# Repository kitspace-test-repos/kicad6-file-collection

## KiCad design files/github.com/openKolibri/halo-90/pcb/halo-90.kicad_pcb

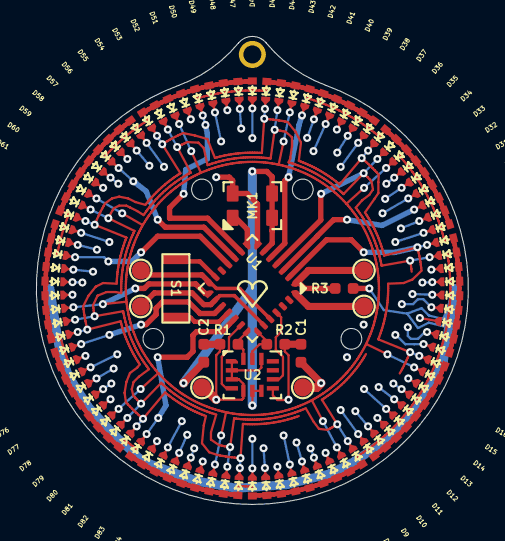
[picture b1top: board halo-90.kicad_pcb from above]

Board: 4 copper layers, 24.0 x 26.0 mm, 111 parts (1 on the bottom side), 23 nets.

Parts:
BT1: CR-2032; BAT-HLD-001-HALO
C1: 0u1; C-0402
C2: 1u; C-0402
D1, D2, D3, D4, D5, D6, D7, D8, D9, D10, D11, D12, D13, D14, D15, D16, D17, D18, D19, D20, D21, D22, D23, D24, D25, D26, D27, D28, D29, D30, D31, D32, D33, D34, D35, D36, D37, D38, D39, D40, D41, D42, D43, D44, D45, D46, D47, D48, D49, D50, D51, D52, D53, D54, D55, D56, D57, D58, D59, D60, D61, D62, D63, D64, D65, D66, D67, D68, D69, D70, D71, D72, D73, D74, D75, D76, D77, D78, D79, D80, D81, D82, D83, D84, D85, D86, D87, D88, D89, D90: LED; D-0402
H1: frenchEarwire; earringHookWire
MH1, MH2, MH3, MH4: toolingHole; 1.152mm-ToolingHole
MK1: SPW2430HR5H-B
R1, R2, R3: 10k; R-0402
S1: KXT3
TP1: TX; TestPoint_Pad_D1.0mm
TP2: SWIM; TestPoint_Pad_D1.0mm
TP3: GND; TestPoint_Pad_D1.0mm
TP4: 3V0; TestPoint_Pad_D1.0mm
TP5: RST; TestPoint_Pad_D1.0mm
TP6: RX; TestPoint_Pad_D1.0mm
U1: UFQFPN28
U2: LSM6DSM; LGA-14_3x2.5mm_6-6

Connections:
+3V: BT1.1 (+), C1.1, C2.1, MK1.4 (VDD), R1.2, R2.2, R3.1, TP4.1, U1.7 (VDD), U2.1 (SDO/SA0), U2.2 (SDX), U2.3 (SCX), U2.5 (VDDIO), U2.8 (VDD), U2.12 (CS)
CPX-0: D1.2 (K), D2.2 (K), D3.2 (K), D4.2 (K), D5.2 (K), D6.2 (K), D7.2 (K), D8.2 (K), D9.2 (K), D18.1 (A), D27.1 (A), D36.1 (A), D45.1 (A), D54.1 (A), D63.1 (A), D72.1 (A), D81.1 (A), D90.1 (A), U1.2 (PA2)
CPX-1: D9.1 (A), D10.2 (K), D11.2 (K), D12.2 (K), D13.2 (K), D14.2 (K), D15.2 (K), D16.2 (K), D17.2 (K), D18.2 (K), D26.1 (A), D35.1 (A), D44.1 (A), D53.1 (A), D62.1 (A), D71.1 (A), D80.1 (A), D89.1 (A), U1.4 (PA4)
CPX-2: D8.1 (A), D17.1 (A), D19.2 (K), D20.2 (K), D21.2 (K), D22.2 (K), D23.2 (K), D24.2 (K), D25.2 (K), D26.2 (K), D27.2 (K), D34.1 (A), D43.1 (A), D52.1 (A), D61.1 (A), D70.1 (A), D79.1 (A), D88.1 (A), U1.15 (PB3)
CPX-3: D7.1 (A), D16.1 (A), D25.1 (A), D28.2 (K), D29.2 (K), D30.2 (K), D31.2 (K), D32.2 (K), D33.2 (K), D34.2 (K), D35.2 (K), D36.2 (K), D42.1 (A), D51.1 (A), D60.1 (A), D69.1 (A), D78.1 (A), D87.1 (A), U1.5 (PA5)
CPX-4: D6.1 (A), D15.1 (A), D24.1 (A), D33.1 (A), D37.2 (K), D38.2 (K), D39.2 (K), D40.2 (K), D41.2 (K), D42.2 (K), D43.2 (K), D44.2 (K), D45.2 (K), D50.1 (A), D59.1 (A), D68.1 (A), D77.1 (A), D86.1 (A), U1.9 (PD1)
CPX-5: D5.1 (A), D14.1 (A), D23.1 (A), D32.1 (A), D41.1 (A), D46.2 (K), D47.2 (K), D48.2 (K), D49.2 (K), D50.2 (K), D51.2 (K), D52.2 (K), D53.2 (K), D54.2 (K), D58.1 (A), D67.1 (A), D76.1 (A), D85.1 (A), U1.10 (PD2)
CPX-6: D4.1 (A), D13.1 (A), D22.1 (A), D31.1 (A), D40.1 (A), D49.1 (A), D55.2 (K), D56.2 (K), D57.2 (K), D58.2 (K), D59.2 (K), D60.2 (K), D61.2 (K), D62.2 (K), D63.2 (K), D66.1 (A), D75.1 (A), D84.1 (A), U1.11 (PD3)
CPX-7: D3.1 (A), D12.1 (A), D21.1 (A), D30.1 (A), D39.1 (A), D48.1 (A), D57.1 (A), D64.2 (K), D65.2 (K), D66.2 (K), D67.2 (K), D68.2 (K), D69.2 (K), D70.2 (K), D71.2 (K), D72.2 (K), D74.1 (A), D83.1 (A), U1.3 (PA3)
CPX-8: D2.1 (A), D11.1 (A), D20.1 (A), D29.1 (A), D38.1 (A), D47.1 (A), D56.1 (A), D65.1 (A), D73.2 (K), D74.2 (K), D75.2 (K), D76.2 (K), D77.2 (K), D78.2 (K), D79.2 (K), D80.2 (K), D81.2 (K), D82.1 (A), U1.19 (PB7)
CPX-9: D1.1 (A), D10.1 (A), D19.1 (A), D28.1 (A), D37.1 (A), D46.1 (A), D55.1 (A), D64.1 (A), D73.1 (A), D82.2 (K), D83.2 (K), D84.2 (K), D85.2 (K), D86.2 (K), D87.2 (K), D88.2 (K), D89.2 (K), D90.2 (K), U1.17 (PB5)
GND: BT1.2 (-), C1.2, C2.2, MK1.2 (GND), MK1.3 (GND), TP3.1, U2.6 (GND), U2.7 (GND)
MIC: MK1.1 (Output), U1.8 (PD0)
unnamed: R3.2, TP5.1, U1.1 (~NRST)
unnamed: TP2.1, U1.28 (SWIM)
RX: TP6.1, U1.16 (PB4), U1.23 (PC2)
SCL: R2.1, U1.22 (PC1), U2.13 (SCL)
SDA: R1.1, U1.21 (PC0), U2.14 (SDA)
SW-A: S1.1, U1.13 (PB1)
SW-B: S1.2, U1.18 (PB6)
TX: TP1.1, U1.14 (PB2), U1.24 (PC3)
XL-INT1: U1.20 (PD4), U2.4 (INT1)
XL-INT2: U1.25 (PC4), U2.9 (INT2)

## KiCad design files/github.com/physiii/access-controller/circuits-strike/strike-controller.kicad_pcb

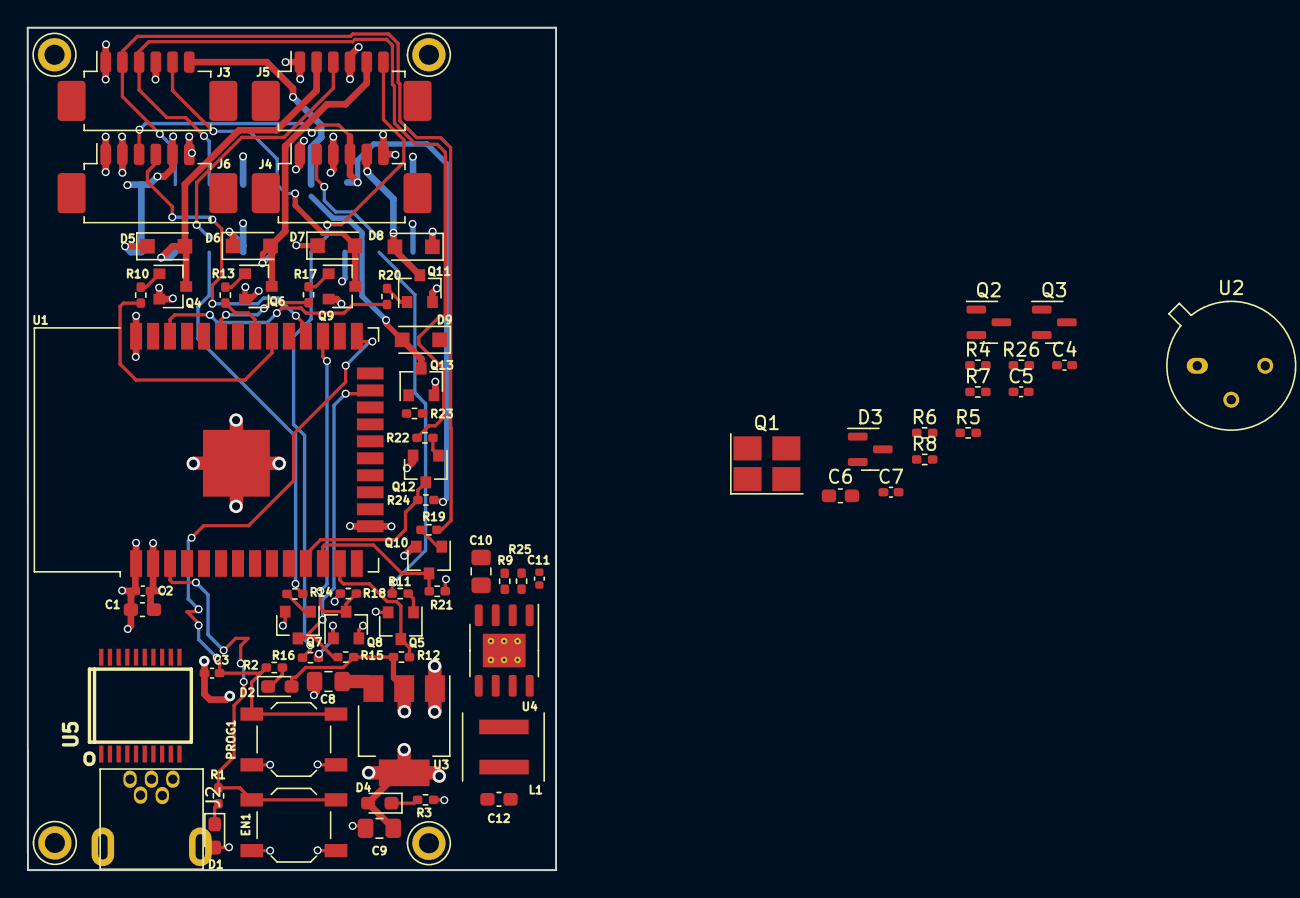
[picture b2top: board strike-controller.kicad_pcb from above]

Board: 4 copper layers, 39.5 x 63.0 mm, 78 parts (1 on the bottom side), 57 nets.

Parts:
C1: C_10uF; C_0603_1608Metric_Pad1.08x0.95mm_HandSolder
C2, C3: C_1uF; C_0402_1005Metric_Pad0.74x0.62mm_HandSolder
C4, C5: C_27pF_0402; C_0402_1005Metric_Pad0.74x0.62mm_HandSolder
C6, C12: C_22uF; C_0603_1608Metric_Pad1.08x0.95mm_HandSolder
C7: C_100nF_0402; C_0402_1005Metric_Pad0.74x0.62mm_HandSolder
C8, C9, C10: C_10uF; C_0805_2012Metric_Pad1.18x1.45mm_HandSolder
C11: 22nF; C_0402_1005Metric
D1, D2: LED_G; D_0603_1608Metric_Pad1.05x0.95mm_HandSolder
D3: BAT54C; SOT-23
D4: LED_G; LED_0603_1608Metric_Pad1.05x0.95mm_HandSolder
D5, D6, D7, D8, D9: D_SM4007PL; D_SOD-123F
EN1: SW_PUSH_SM; SW_SPST_TL3342
J1: Conn_02x09_Odd_Even; PinHeader_2x09_P2.54mm_Vertical_SMD
J2: USB_MINI_B; USB-mini-B-0548190519
J3, J4, J5, J6: Molex_Blade_6pin; Molex_PicoBlade_53261-0671_1x06-1MP_P1.25mm_Horizontal
J7, J8, J9, J10: Conn_01x01_Female; Mount_Hole_1p5
L1: 10uH; L_4x4
PROG1: SW_PUSH_SM; SW_SPST_TL3342
Q1: Crystal_12Mhz; Crystal_SMD_3225-4Pin_3.2x2.5mm_HandSoldering
Q2: Q_SS8050; SOT-23
Q3: Q_SS8550; SOT-23
Q4, Q5, Q6, Q7, Q8, Q9, Q10, Q11, Q12, Q13: Q_MMBT5551; SOT-23
R1, R2, R4, R5, R26: R_10K_0402; R_0402_1005Metric_Pad0.72x0.64mm_HandSolder
R3, R6, R7, R11, R12, R14, R15, R16, R18, R19, R21, R22, R24: R_1K_0402; R_0402_1005Metric_Pad0.72x0.64mm_HandSolder
R8: R_220_0402; R_0402_1005Metric_Pad0.72x0.64mm_HandSolder
R9: 49.9K; R_0402_1005Metric_Pad0.72x0.64mm_HandSolder
R10, R13, R17, R20, R23: R_100; R_0402_1005Metric_Pad0.72x0.64mm_HandSolder
R25: 19K; R_0402_1005Metric_Pad0.72x0.64mm_HandSolder
U1: ESP32-WROOM-32
U2: PIR-DIGITAL; TO-5-3
U3: REG_AMS1117-3.3; SOT-223-3_TabPin2
U4: REG_MT2492; SOIC-8-1EP_3.9x4.9mm_P1.27mm_EP2.514x3.2mm_ThermalVias
U5: CH340T(SSOP20W); SSOP-20W

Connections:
+3V3: C1.1, C2.1, C9.1, D1.2 (A), D2.2 (A), D4.2 (A), J1.13, J4.4, J6.3, R12.2, R15.2, R18.2, R21.2, R24.2, R26.2, U1.2 (VDD), U3.2 (Vout)
/5V: C6.1, C8.1, C12.1, J2.1 (VBUS), L1.2, R4.1, R9.1, U3.3 (Vin), U5.19 (VCC)
/AUX: D9.2 (A), J1.11, J3.6, Q13.3 (C)
/AUX_IO: R23.1, U1.37 (IO23)
/BUZZER1: D8.2 (A), J1.15, J4.5, Q11.3 (C)
/BUZZER1_IO: R20.1, U1.36 (IO22)
/CONTACT1: J1.6, J5.3, R14.2
/CONTACT1_IO: Q7.3 (C), R15.1, U1.23 (IO15)
/CONTACT2: J1.12, J5.6, R16.2
/CONTACT2_IO: Q8.3 (C), R18.1, U1.27 (IO16)
/ESP_EN: EN1.1, Q2.3 (C), R1.1, U1.3 (EN)
/EXIT: J1.16, J4.2, R11.2
/EXIT_IO: Q5.3 (C), R12.1, U1.13 (IO14)
/IO2: D3.2 (A2), U1.24 (IO2)
/IO17: J6.4, U1.28 (IO17)
/KEYPAD_PUSH: D7.2 (A), J1.9, J3.5, Q9.3 (C)
/KEYPAD_PUSH_IO: R17.1, U1.33 (IO21)
/LOCK1: D5.2 (A), J1.4, J5.2, Q4.3 (C)
/LOCK1_IO: R10.1, U1.30 (IO18)
/LOCK2: D6.2 (A), J1.10, J5.5, Q6.3 (C)
/LOCK2_IO: R13.1, U1.31 (IO19)
/POWER: C10.1, D5.1 (K), D6.1 (K), D7.1 (K), D8.1 (K), D9.1 (K), J1.1, J1.2, J1.8, J1.14, J3.1, J4.1, J5.1, J5.4, J6.2, J6.5, U4.4 (EN), U4.5 (VIN)
/PROG: C3.1, D3.1 (A1), PROG1.1, R2.1, U1.25 (IO0)
/RX: R5.2, R26.1, U1.34 (RXD0/IO3), U5.3 (TXD)
/TX: R4.2, U1.35 (TXD0/IO1), U5.4 (RXD)
/USB/D+: J2.3 (D+), U5.6 (UD+)
/USB/D-: J2.2 (D-), U5.7 (UD-)
/USB/D_Com: D3.3 (CC), R8.1
/WG_D0: J1.3, J3.2, R19.2
/WG_D0_IO: Q10.3 (C), R21.1, U1.12 (IO27)
/WG_D1: J1.5, J3.3, R22.2
/WG_D1_IO: Q12.3 (C), R24.1, U1.11 (IO26)
GND: C1.2, C2.2, C3.2, C4.2, C5.2, C6.2, C7.2, C8.2, C9.2, C10.2, C12.2, EN1.2, J1.7, J1.17, J1.18, J2.5 (GND), J3.4, J4.3, J4.6, J6.1, J6.6, J7.1, J8.1, J9.1, J10.1, PROG1.2, Q1.2 (case), Q1.4 (case), Q4.2 (E), Q5.2 (E), Q6.2 (E), Q7.2 (E), Q8.2 (E), Q9.2 (E), Q10.2 (E), Q11.2 (E), Q12.2 (E), Q13.2 (E), R3.2, R25.2, U1.1 (GND), U1.15 (GND), U1.38 (GND), U1.39 (GND), U3.1 (GND), U4.2 (GND), U5.8 (GND)
unnamed: C4.1, Q1.1, U5.9 (XI)
unnamed: C5.1, Q1.3, U5.10 (XO)
unnamed: C7.1, R5.1, U5.5 (V3)
unnamed: C11.1, U4.1 (BS)
unnamed: C11.2, L1.1, U4.6 (SW)
unnamed: D1.1 (K), R1.2
unnamed: D2.1 (K), R2.2
unnamed: D4.1 (K), R3.1
unnamed: Q2.1 (B), R6.1
unnamed: Q2.2 (E), R7.2, U5.16 (RTS#)
unnamed: Q3.1 (B), R7.1
unnamed: Q3.2 (E), R8.2
unnamed: Q3.3 (C), R6.2, U5.15 (DTR#)
unnamed: Q4.1 (B), R10.2
unnamed: Q5.1 (B), R11.1
unnamed: Q6.1 (B), R13.2
unnamed: Q7.1 (B), R14.1
unnamed: Q8.1 (B), R16.1
unnamed: Q9.1 (B), R17.2
unnamed: Q10.1 (B), R19.1
unnamed: Q11.1 (B), R20.2
unnamed: Q12.1 (B), R22.1
unnamed: Q13.1 (B), R23.2
unnamed: R9.2, R25.1, U4.3 (FB)

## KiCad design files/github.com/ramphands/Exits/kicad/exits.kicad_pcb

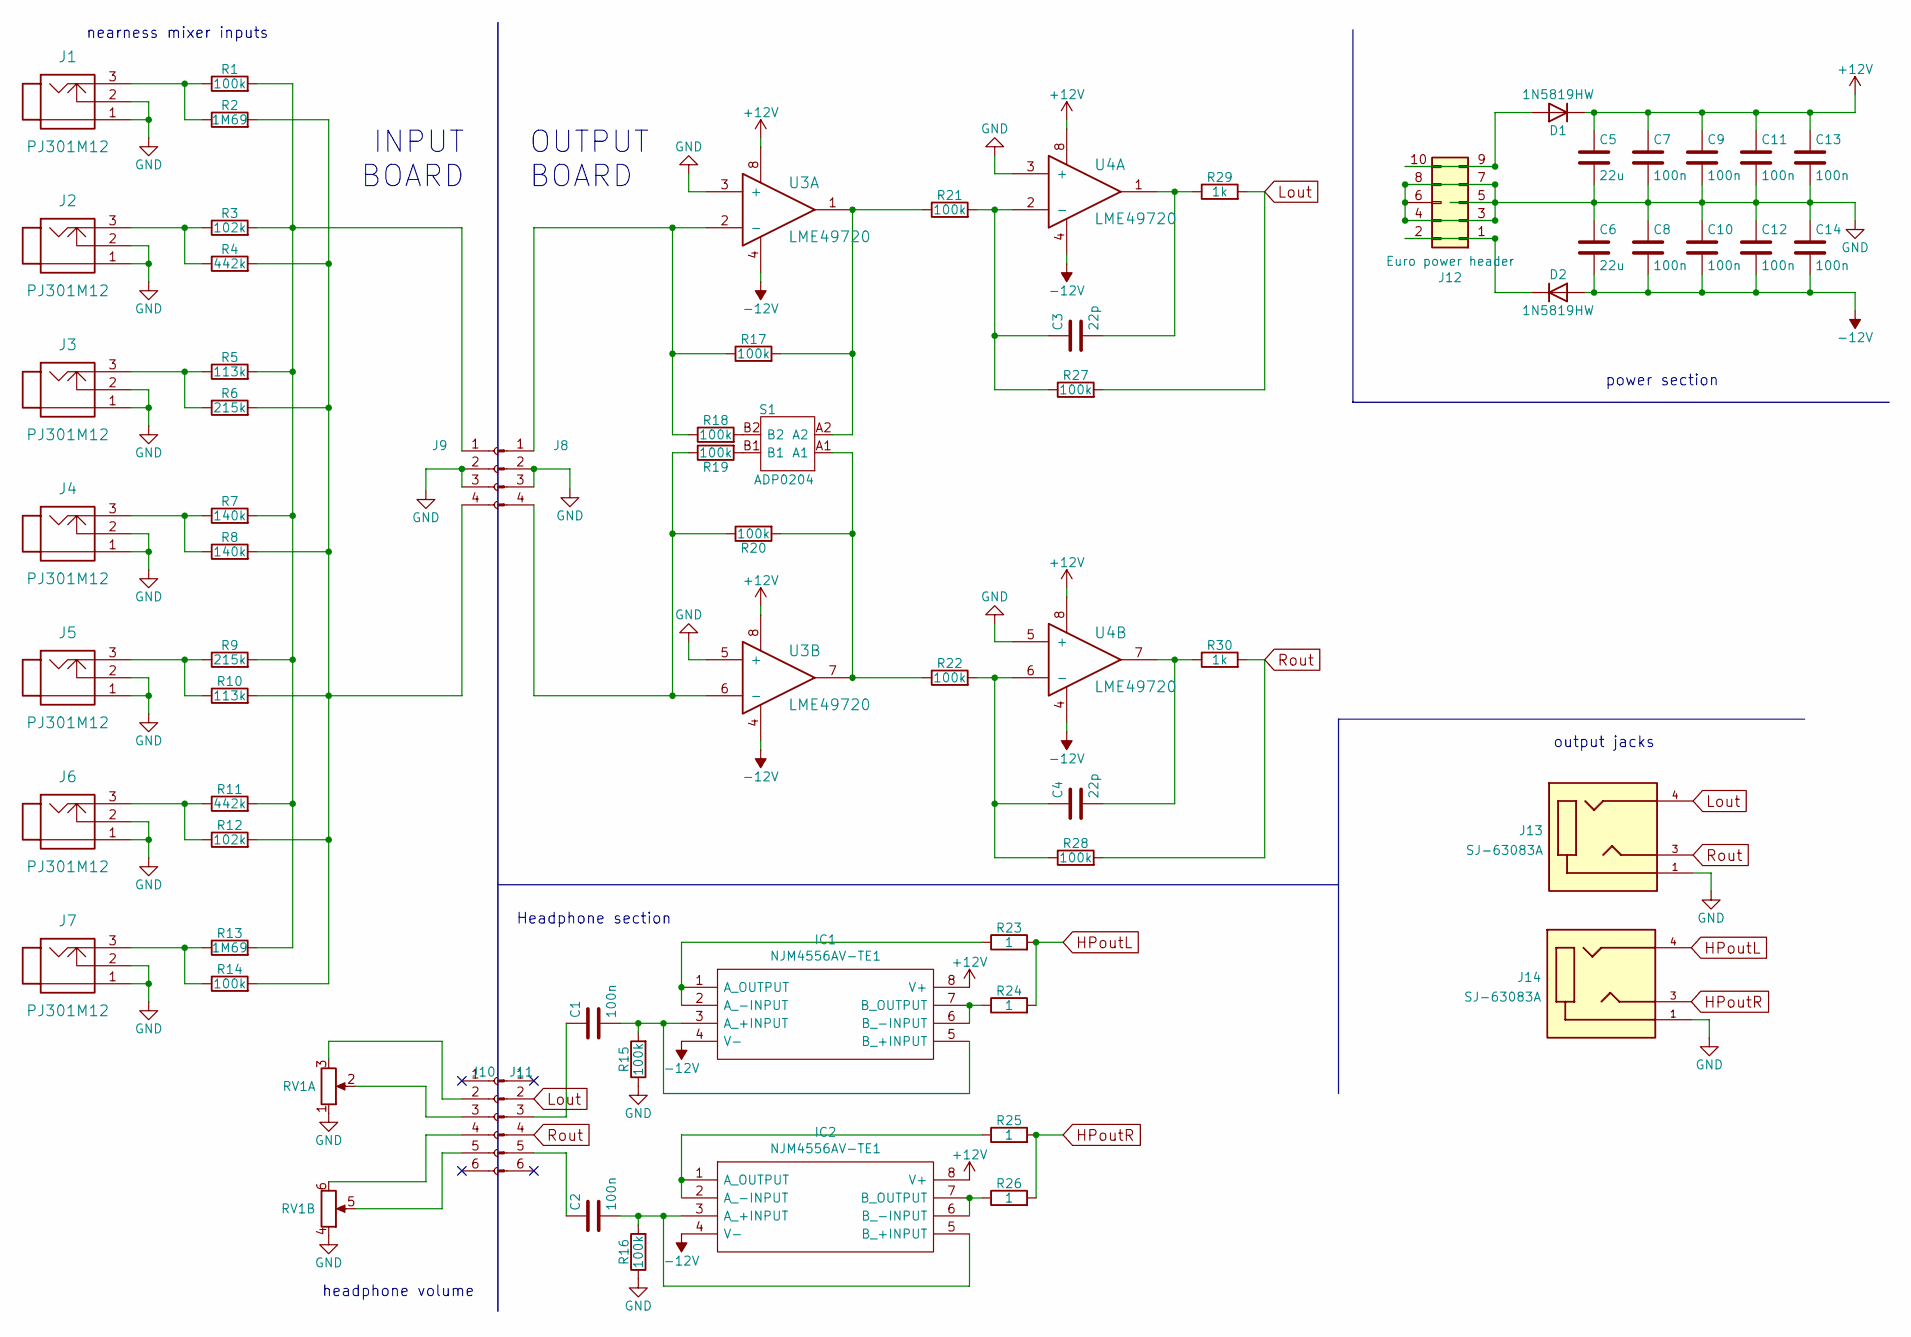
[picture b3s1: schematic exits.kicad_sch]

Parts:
C1, C2: 100n; C_1206
C3, C4: 22p; 0603
C5, C6: 22u; 0805
C7, C8, C9, C10, C11, C12, C13, C14: 100n; 0603
D1, D2: 1N5819HW; SOD-123
IC1, IC2: NJM4556AV-TE1; SOP65P640X145-8N; Mouser Part Number 513-NJM4556AV-TE1
J1, J2, J3, J4, J5, J6, J7: PJ301M12
J8: Conn_01x04_Male; PinHeader_1x04_P2.54mm_Vertical
J9: Conn_01x04_Female; PinSocket_1x04_P2.54mm_Vertical
J10: Conn_01x06_Female; PinSocket_1x06_P2.54mm_Vertical
J11: Conn_01x06_Male; PinHeader_1x06_P2.54mm_Vertical
J12: Euro power header; IDC-Header_2x05_P2.54mm_Vertical
J13, J14: SJ-63083A; CUI_SJ-63083A; PARTREV 1.0
R1, R14, R17, R18, R19, R20, R21, R22, R27, R28: 100k; 0603
R2, R13: 1M69; 0603
R3, R12: 102k; 0603
R4, R11: 442k; 0603
R5, R10: 113k; 0603
R6, R9: 215k; 0603
R7, R8: 140k; 0603
R15, R16: 100k; R_1206_3216Metric
R23, R24, R25, R26: 1; R_1206_3216Metric
R29, R30: 1k; 0603
RV1: 50k A; Potentiometer_Alpha_RD902F-40-00D_Dual_Vertical
S1: ADP0204; Mouser Part Number 506-ADP0204
U3, U4: LME49720; SOIC-8

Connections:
+12V: C5.1, C7.1, C9.1, C11.1, C13.1, D1.1 (K), IC1.8 (V+), IC2.8 (V+), U3.8, U4.8
-12V: C6.2, C8.2, C10.2, C12.2, C14.2, D2.2 (A), IC1.4 (V-), IC2.4 (V-), U3.4, U4.4
GND: C5.2, C6.1, C7.2, C8.1, C9.2, C10.1, C11.2, C12.1, C13.2, C14.1, J1.1, J1.2, J2.1, J2.2, J3.1, J3.2, J4.1, J4.2, J5.1, J5.2, J6.1, J6.2, J7.1, J7.2, J8.2, J8.3, J9.2, J9.3, J12.3, J12.4, J12.5, J12.6, J12.7, J12.8, J13.1, J14.1, R15.1, R16.1, RV1.1, RV1.4, U3.3 (+), U3.5 (+), U4.3 (+), U4.5 (+)
HPoutL: J14.4, R23.2, R24.2
HPoutR: J14.3, R25.2, R26.2
Lout: J11.2, J13.4, R27.2, R29.2
unnamed: C1.1, J11.3
unnamed: C1.2, IC1.3 (A_+INPUT), IC1.5 (B_+INPUT), R15.2
unnamed: C2.1, J11.5
unnamed: C2.2, IC2.3 (A_+INPUT), IC2.5 (B_+INPUT), R16.2
unnamed: C3.1, R21.2, R27.1, U4.2 (-)
unnamed: C3.2, R29.1, U4.1
unnamed: C4.1, R22.2, R28.1, U4.6 (-)
unnamed: C4.2, R30.1, U4.7
unnamed: D1.2 (A), J12.9, J12.10
unnamed: D2.1 (K), J12.1, J12.2
unnamed: IC1.1 (A_OUTPUT), IC1.2 (A_-INPUT), R23.1
unnamed: IC1.6 (B_-INPUT), IC1.7 (B_OUTPUT), R24.1
unnamed: IC2.1 (A_OUTPUT), IC2.2 (A_-INPUT), R25.1
unnamed: IC2.6 (B_-INPUT), IC2.7 (B_OUTPUT), R26.1
unnamed: J1.3, R1.1, R2.1
unnamed: J2.3, R3.1, R4.1
unnamed: J3.3, R5.1, R6.1
unnamed: J4.3, R7.1, R8.1
unnamed: J5.3, R9.1, R10.1
unnamed: J6.3, R11.1, R12.1
unnamed: J7.3, R13.1, R14.1
unnamed: J8.1, R17.1, R18.1, U3.2 (-)
unnamed: J8.4, R19.1, R20.1, U3.6 (-)
unnamed: J9.1, R1.2, R3.2, R5.2, R7.2, R9.2, R11.2, R13.2
unnamed: J9.4, R2.2, R4.2, R6.2, R8.2, R10.2, R12.2, R14.2
unnamed: J10.2, RV1.3
unnamed: J10.3, RV1.2
unnamed: J10.4, RV1.6
unnamed: J10.5, RV1.5
unnamed: R17.2, R21.1, S1.A2, U3.1
unnamed: R18.2, S1.B2
unnamed: R19.2, S1.B1
unnamed: R20.2, R22.1, S1.A1, U3.7
Rout: J11.4, J13.3, R28.2, R30.2

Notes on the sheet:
headphone volume
INPUT BOARD
Headphone section
OUTPUT BOARD
output jacks
nearness mixer inputs
power section

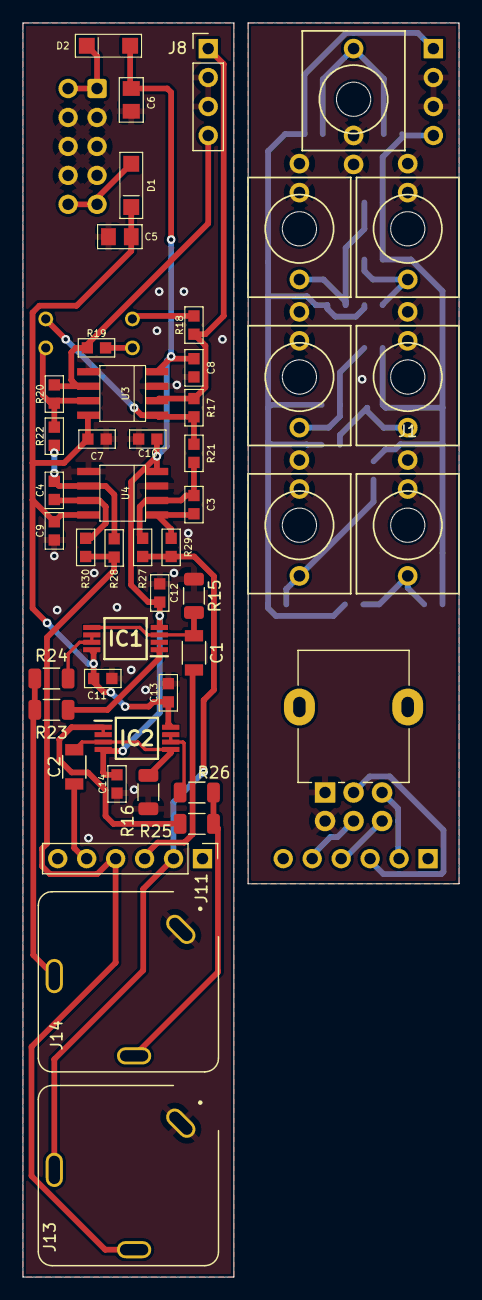
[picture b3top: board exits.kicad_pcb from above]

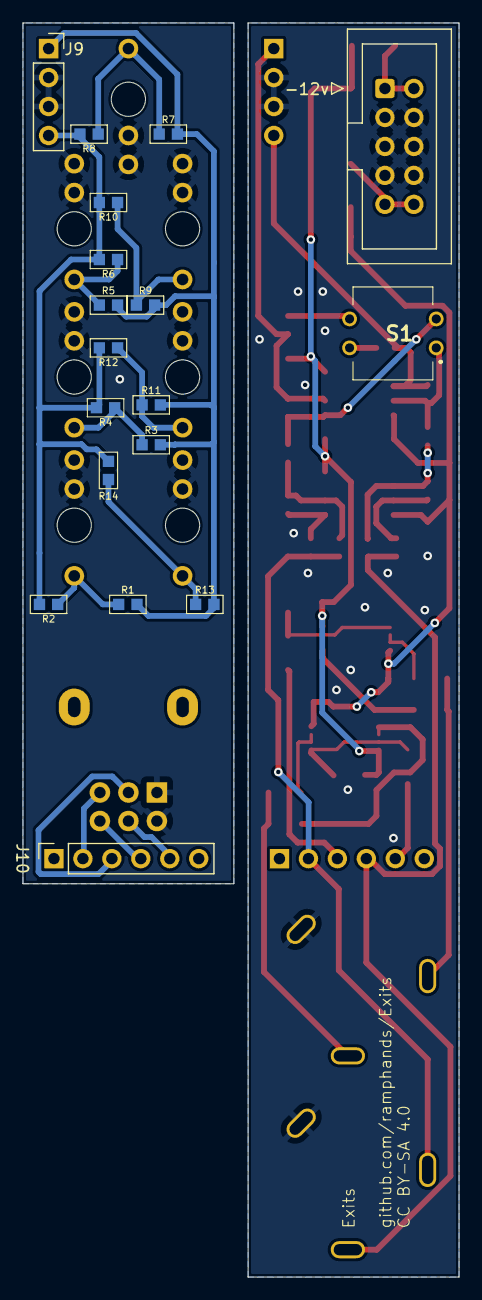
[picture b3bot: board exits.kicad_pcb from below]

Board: 2 copper layers, 38.2 x 110.0 mm, 66 parts (18 on the bottom side), 40 nets.

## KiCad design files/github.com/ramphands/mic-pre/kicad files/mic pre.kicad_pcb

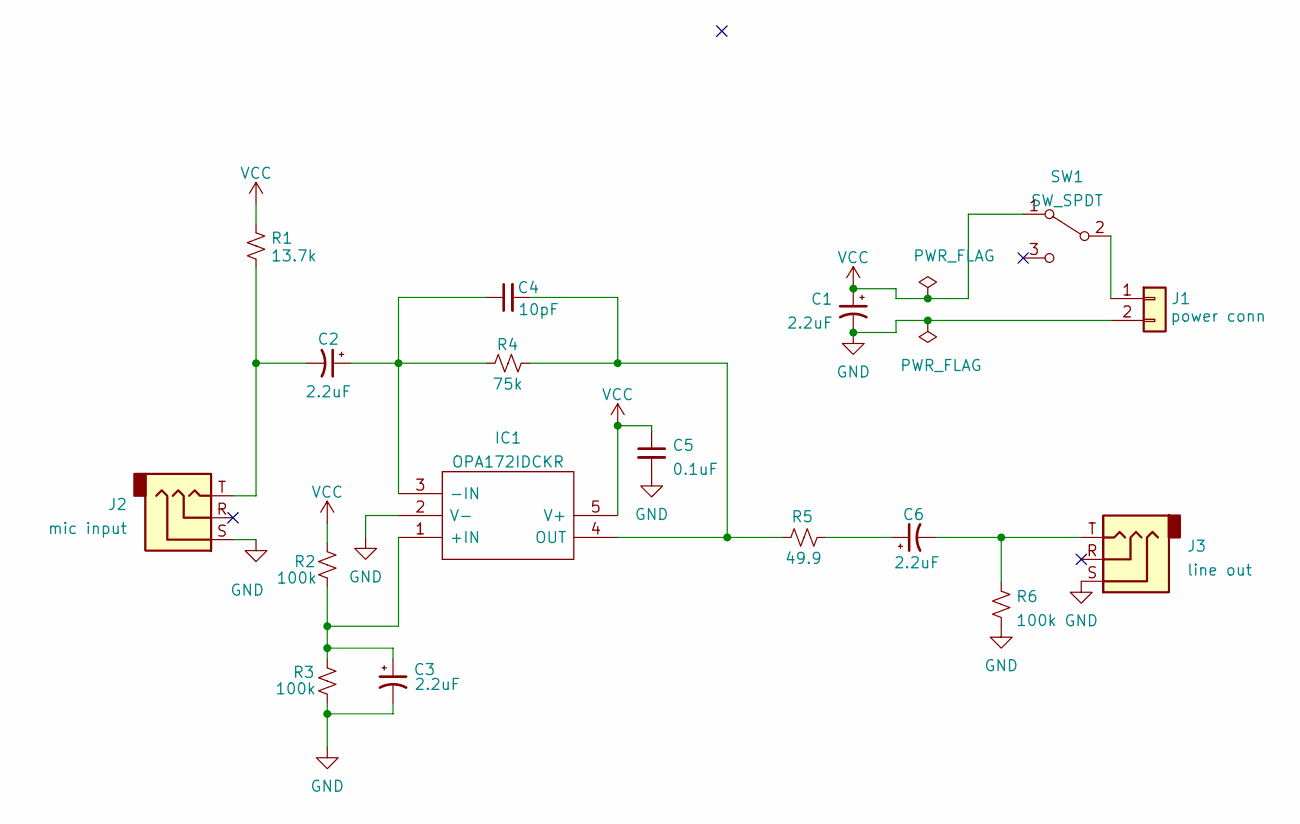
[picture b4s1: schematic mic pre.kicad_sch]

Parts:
C1, C2, C3, C6: 2.2uF; CP_EIA-3216-18_Kemet-A_Pad1.58x1.35mm_HandSolder
C4: 10pF; C_0603_1608Metric_Pad1.08x0.95mm_HandSolder
C5: 0.1uF; C_0603_1608Metric_Pad1.08x0.95mm_HandSolder
IC1: OPA172IDCKR; SOT-353_SC-70-5_Handsoldering; Mouser Part Number 595-OPA172IDCKR
J1: power conn; PinSocket_1x02_P2.54mm_Vertical
J2: mic input; CUI_SJ1-3523N
J3: line out; CUI_SJ1-3523N
R1: 13.7k; R_0603_1608Metric_Pad0.98x0.95mm_HandSolder
R2, R3, R6: 100k; R_0603_1608Metric_Pad0.98x0.95mm_HandSolder
R4: 75k; R_0603_1608Metric_Pad0.98x0.95mm_HandSolder
R5: 49.9; R_0603_1608Metric_Pad0.98x0.95mm_HandSolder
SW1: SW_SPDT; LSS12-V-B

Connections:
GND: C1.2, C3.2, C5.2, IC1.2 (V-), J1.2, J2.S, J3.S, R3.2, R6.2
unnamed: C2.1, C4.1, IC1.3 (-IN), R4.1
unnamed: C2.2, J2.T, R1.2
unnamed: C3.1, IC1.1 (+IN), R2.2, R3.1
unnamed: C4.2, IC1.4 (OUT), R4.2, R5.1
unnamed: C6.1, R5.2
unnamed: C6.2, J3.T, R6.1
unnamed: J1.1, SW1.2 (B)
VCC: C1.1, C5.1, IC1.5 (V+), R1.1, R2.1, SW1.1 (A)

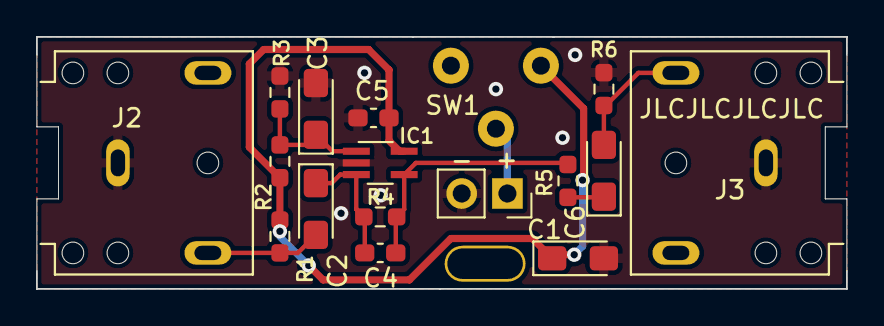
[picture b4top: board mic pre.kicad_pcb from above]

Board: 2 copper layers, 45.0 x 14.0 mm, 17 parts (0 on the bottom side), 9 nets.

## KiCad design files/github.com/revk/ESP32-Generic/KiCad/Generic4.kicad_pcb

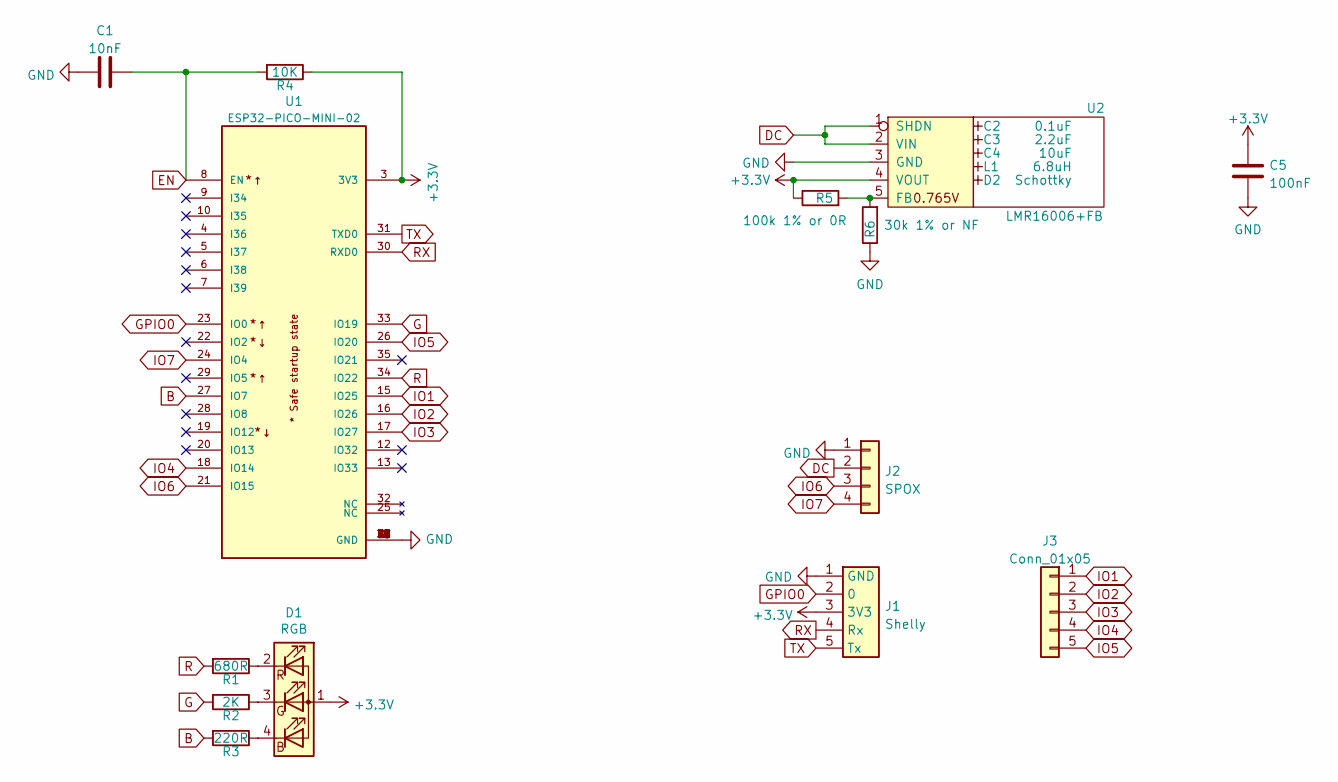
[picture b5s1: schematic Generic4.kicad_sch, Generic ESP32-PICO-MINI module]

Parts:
C1: 10nF; C_0603
C2: 0.1uF; Hidden
C3: 2.2uF; Hidden
C4: 10uF; Hidden
C5: 100nF; C_0603
D1: RGB; LED-RGB-1.6x1.6; Part No APTF1616LSEEZGKQBKC
D2: Schottky; Hidden; Part No CD1206-B2100
J1: Shelly
J2: SPOX; Molex_MiniSPOX_H4RA
J3: Conn_01x05; PinSocket_1x05_P2.54mm_Vertical
L1: 6.8uH; Hidden; Part No TYA4020
R1: 680R; R_0603
R2: 2K; R_0603
R3: 220R; R_0603
R4: 10K; R_0603
R5: 100k 1% or 0R; R_0603
R6: 30k 1% or NF; R_0603
U1: ESP32-PICO-MINI-02; PARTREV v1.0
U2: LMR16006+FB; RegulatorBlockFB; Part No LMR16006YQ3

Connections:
+3V3: C5.1, D1.1 (A), J1.3 (3V3), R4.1, R5.1, U1.3 (3V3), U2.4 (VOUT)
B: R3.2, U1.27 (IO7)
DC: J2.2, U2.1 (SHDN), U2.2 (VIN)
EN: C1.2, R4.2, U1.8 (EN)
G: R2.2, U1.33 (IO19)
GND: C1.1, C5.2, J1.1 (GND), J2.1, R6.1, U1.1 (GND), U1.2 (GND), U1.11 (GND), U1.14 (GND), U1.36 (GND), U1.37 (GND), U1.38 (GND), U1.39 (GND), U1.40 (GND), U1.41 (GND), U1.42 (GND), U1.43 (GND), U1.44 (GND), U1.45 (GND), U1.46 (GND), U1.47 (GND), U1.48 (GND), U1.49 (GND), U1.50 (GND), U1.51 (GND), U1.52 (GND), U1.53 (GND), U2.3 (GND)
GPIO0: J1.2 (0), U1.23 (IO0)
IO1: J3.1, U1.15 (IO25)
IO2: J3.2, U1.16 (IO26)
IO3: J3.3, U1.17 (IO27)
IO4: J3.4, U1.18 (IO14)
IO5: J3.5, U1.26 (IO20)
IO6: J2.3, U1.21 (IO15)
IO7: J2.4, U1.24 (IO4)
unnamed: D1.2 (RK), R1.1
unnamed: D1.3 (GK), R2.1
unnamed: D1.4 (BK), R3.1
unnamed: R5.2, R6.2, U2.5 (FB)
R: R1.2, U1.34 (IO22)
RX: J1.4 (Rx), U1.30 (RXD0)
TX: J1.5 (Tx), U1.31 (TXD0)

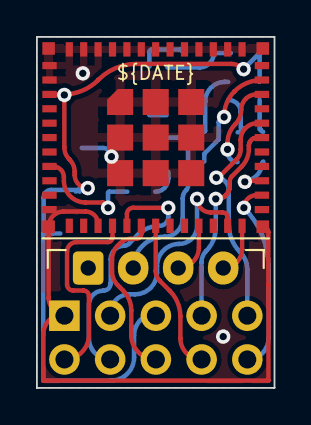
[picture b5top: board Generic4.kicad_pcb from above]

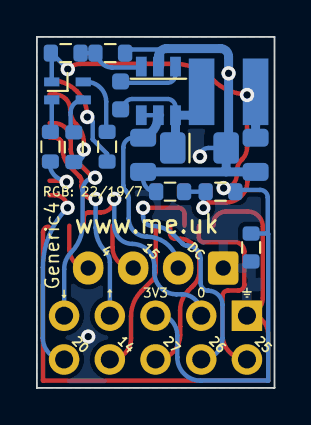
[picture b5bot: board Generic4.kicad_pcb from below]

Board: 2 copper layers, 13.2 x 19.5 mm, 19 parts (16 on the bottom side), 21 nets.

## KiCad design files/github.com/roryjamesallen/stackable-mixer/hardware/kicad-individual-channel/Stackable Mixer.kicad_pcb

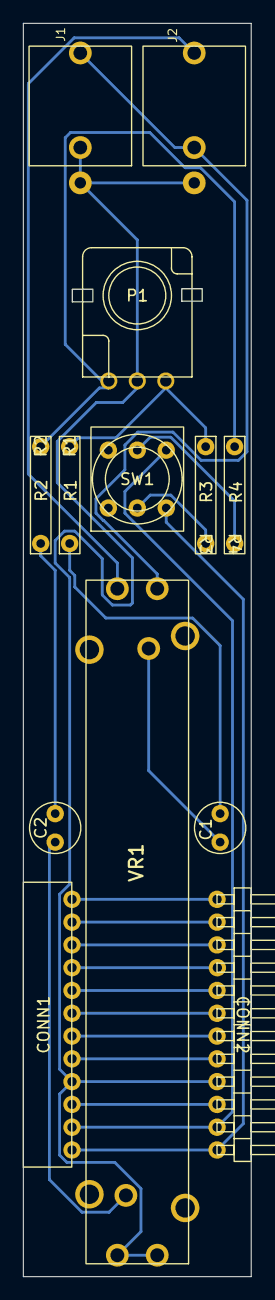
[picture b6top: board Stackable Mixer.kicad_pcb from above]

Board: 2 copper layers, 20.0 x 110.0 mm, 13 parts (0 on the bottom side), 22 nets.

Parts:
C1, C2: 100nF; Capacitor Small Non-Polarised
CONN1: Header_2.0mm_Right_Angle_Female; Header 01x12 2.0mm Right Angle Female
CONN2: Header_2.0mm_Right_Angle_Male; Header 01x12 2.0mm Right Angle Male
J1: L/Mono; Thonkiconn Mono Jack
J2: R; Thonkiconn Mono Jack
P1: Potentiometer_9mm_Vertical_Linear; Potentiometer 9mm Vertical Linear
R1, R2: 100k; Resistor 0.25W Through-Hole
R3, R4: 4.7k; Resistor 0.25W Through-Hole
SW1: SW_DPDT_x2; Sub-Miniature Toggle Switch DPDT
VR1: Potentiometer_45mm_Slide_Audio_Dual; Potentiometer 45mm Slide Audio

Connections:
/+12V: CONN1.5, CONN2.8
/-12V: CONN1.3, CONN2.10
/LEFT BUS: CONN1.1, CONN2.12, SW1.1 (A)
/LEFT SIGNAL: R3.2, SW1.2 (B)
/RIGHT BUS: CONN1.2, CONN2.11, SW1.4 (A)
/RIGHT SIGNAL: R4.2, SW1.5 (B)
Earth: CONN1.4, CONN2.9, J1.1 (E), J1.2 (S), J2.1 (E), P1.2, VR1.1, VR1.4
unnamed: C1.1, VR1.5
unnamed: C1.2, R1.1
unnamed: C2.1, VR1.2
unnamed: C2.2, R2.1
unnamed: CONN1.6, CONN2.7
unnamed: CONN1.7, CONN2.6
unnamed: CONN1.8, CONN2.5
unnamed: CONN1.9, CONN2.4
unnamed: CONN1.10, CONN2.3
unnamed: CONN1.11, CONN2.2
unnamed: CONN1.12, CONN2.1
unnamed: J1.3 (T), J2.2 (S), VR1.6
unnamed: J2.3 (T), VR1.3
unnamed: P1.1, R2.2, R4.1
unnamed: P1.3, R1.2, R3.1

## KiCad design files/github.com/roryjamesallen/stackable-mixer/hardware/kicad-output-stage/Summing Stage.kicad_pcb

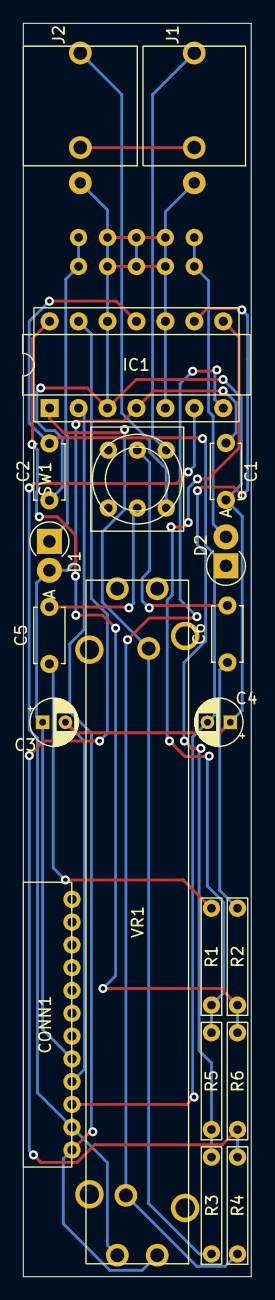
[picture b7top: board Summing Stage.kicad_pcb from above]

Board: 2 copper layers, 20.0 x 110.0 mm, 21 parts (1 on the bottom side), 18 nets.

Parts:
C1, C2, C5, C6: 100n; C_Disc_D4.7mm_W2.5mm_P5.00mm
C3, C4: 10u; CP_Radial_D4.0mm_P2.00mm
CONN1: Header_2.0mm_Right_Angle_Female; Header 01x12 2.0mm Right Angle Female
D1, D2: DIODE; D_DO-41_SOD81_P2.54mm_Vertical_AnodeUp
IC1: TL074; DIP-14 IC Socket
J1: Thonkiconn_Mono_Jack; Thonkiconn Mono Jack
J2: AudioJack3; Thonkiconn Stereo Jack
PowerHeader1: Conn_02x05_Counter_Clockwise; Eurorack Power Header
R1, R2: 1k; Resistor 0.25W Through-Hole
R3, R4, R5, R6: 4.7k; Resistor 0.25W Through-Hole
SW1: SW_DPDT_x2; Sub-Miniature Toggle Switch DPDT
VR1: Potentiometer_45mm_Slide_Audio_Dual; Potentiometer 45mm Slide Audio

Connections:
+12V: C1.1, C3.1, CONN1.5, D1.2 (K), IC1.4 (V+)
-12V: C2.2, C4.2, CONN1.3, D2.1 (A), IC1.11 (V-)
Earth: C1.2, C2.1, C3.2, C4.1, CONN1.4, IC1.3 (+), IC1.5 (+), IC1.10 (+), IC1.12 (+), J1.1 (E), PowerHeader1.3, PowerHeader1.4, PowerHeader1.5, PowerHeader1.6, PowerHeader1.7, PowerHeader1.8
unnamed: C5.1, R1.2
unnamed: C5.2, SW1.2 (B)
unnamed: C6.1, R2.2
unnamed: C6.2, SW1.5 (B)
unnamed: CONN1.1, IC1.2 (-), VR1.4
unnamed: CONN1.2, IC1.6 (-), VR1.1
unnamed: D1.1 (A), PowerHeader1.9, PowerHeader1.10
unnamed: D2.2 (K), PowerHeader1.1, PowerHeader1.2
unnamed: IC1.1, R3.1, VR1.5
unnamed: IC1.7, R4.1, VR1.2
unnamed: IC1.8, R1.1, R5.2
unnamed: IC1.9 (-), R3.2, R5.1
unnamed: IC1.13 (-), R4.2, R6.1
unnamed: IC1.14, R2.1, R6.2
R OUT: J1.3 (T), SW1.4 (A)

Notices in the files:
files/github.com/ramphands/Exits/kicad/exits.kicad_pcb:
CC BY-SA 4.0
files/github.com/roryjamesallen/stackable-mixer/hardware/kicad-individual-channel/Stackable Mixer.kicad_pcb:
CERN OHL-S v2
